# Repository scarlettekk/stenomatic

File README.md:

Stenomatic is an open source stenotype keyboard designed for an elegant yet inexpensive typing experience. This repository hosts all the files and information needed to produce one, which anyone can do for their own use. You may use your Stenomatic for any purpose you like, but you may not produce Stenomatics for the express purpose of selling them.

*Note: Photos of the keyboard in this document are of v2.0, when the Left S and * keys were rotated incorrectly, hence they only had 1u keycaps. This is fixed in the current version and 2u keycaps can be used.*

Stenomatic uses [Kailh Choc Pink switches](https://www.kailhswitch.com/mechanical-keyboard-switches/choc-pro-pink-keyboard-switch.html) for the most similar experience to a professional stenotype machine.

[Stenomatic](https://github.com/scarlettekk/stenomatic) © 2024 by [Cora Shuryn](https://github.com/scarlettekk/) is licensed under [CC BY-NC-SA 4.0](https://creativecommons.org/licenses/by-nc-sa/4.0/?ref=chooser-v1)

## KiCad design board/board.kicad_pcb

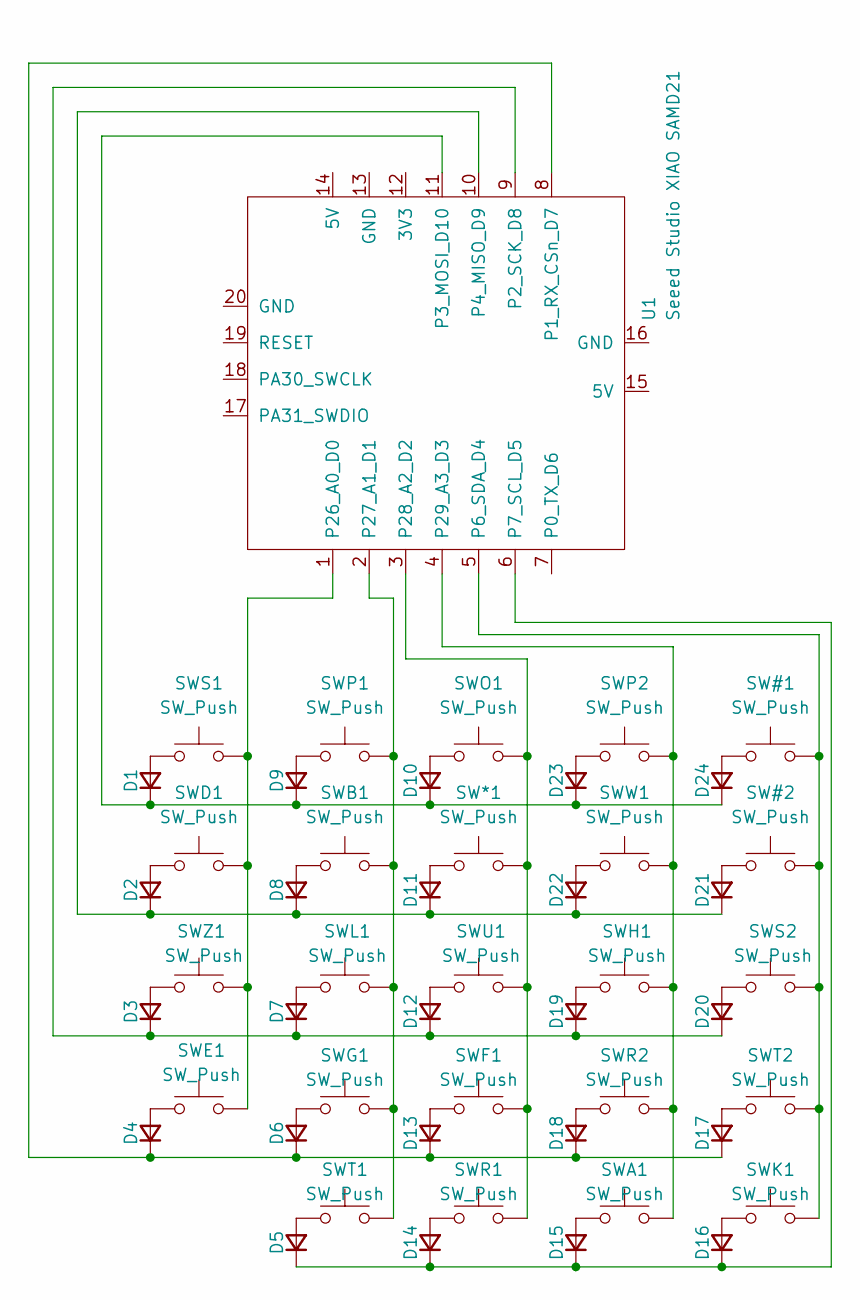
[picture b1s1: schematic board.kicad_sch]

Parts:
D1, D2, D3, D4, D5, D6, D7, D8, D9, D10, D11, D12, D13, D14, D15, D16, D17, D18, D19, D20, D21, D22, D23, D24: D_Small; D_DO-41_SOD81_P7.62mm_Horizontal
SW#1, SW#2: SW_Push; SW_Matias_1.00u
SW*1: SW_Push; SW_Matias_1.00u
SWA1: SW_Push; SW_Matias_1.00u
SWB1: SW_Push; SW_Matias_1.00u
SWD1: SW_Push; SW_Matias_1.00u
SWE1: SW_Push; SW_Matias_1.00u
SWF1: SW_Push; SW_Matias_1.00u
SWG1: SW_Push; SW_Matias_1.00u
SWH1: SW_Push; SW_Matias_1.00u
SWK1: SW_Push; SW_Matias_1.00u
SWL1: SW_Push; SW_Matias_1.00u
SWO1: SW_Push; SW_Matias_1.00u
SWP1, SWP2: SW_Push; SW_Matias_1.00u
SWR1, SWR2: SW_Push; SW_Matias_1.00u
SWS1, SWS2: SW_Push; SW_Matias_1.00u
SWT1, SWT2: SW_Push; SW_Matias_1.00u
SWU1: SW_Push; SW_Matias_1.00u
SWW1: SW_Push; SW_Matias_1.00u
SWZ1: SW_Push; SW_Matias_1.00u
U1: Seeed Studio XIAO SAMD21; XIAO-SAMD21-RP2040-14P-2.54-21X17.8MM (Seeeduino XIAO)

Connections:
unnamed: D1.2 (A), SWS1.1
unnamed: D1.1 (K), D9.1 (K), D10.1 (K), D23.1 (K), D24.1 (K), U1.11 (P3_MOSI_D10)
unnamed: D2.2 (A), SWD1.1
unnamed: D3.2 (A), SWZ1.1
unnamed: D4.2 (A), SWE1.1
unnamed: D5.2 (A), SWT1.1
unnamed: D6.2 (A), SWG1.1
unnamed: D7.2 (A), SWL1.1
unnamed: D8.2 (A), SWB1.1
unnamed: D9.2 (A), SWP1.1
unnamed: D10.2 (A), SWO1.1
unnamed: D11.2 (A), SW*1.1
unnamed: D2.1 (K), D8.1 (K), D11.1 (K), D21.1 (K), D22.1 (K), U1.10 (P4_MISO_D9)
unnamed: D12.2 (A), SWU1.1
unnamed: D3.1 (K), D7.1 (K), D12.1 (K), D19.1 (K), D20.1 (K), U1.9 (P2_SCK_D8)
unnamed: D13.2 (A), SWF1.1
unnamed: D4.1 (K), D6.1 (K), D13.1 (K), D17.1 (K), D18.1 (K), U1.8 (P1_RX_CSn_D7)
unnamed: D14.2 (A), SWR1.1
unnamed: D5.1 (K), D14.1 (K), D15.1 (K), D16.1 (K), U1.6 (P7_SCL_D5)
unnamed: D15.2 (A), SWA1.2
unnamed: D16.2 (A), SWK1.1
unnamed: D17.2 (A), SWT2.1
unnamed: D18.2 (A), SWR2.2
unnamed: D19.2 (A), SWH1.2
unnamed: D20.2 (A), SWS2.1
unnamed: D21.2 (A), SW#2.1
unnamed: D22.2 (A), SWW1.2
unnamed: D23.2 (A), SWP2.2
unnamed: D24.2 (A), SW#1.1
unnamed: SW#1.2, SW#2.2, SWK1.2, SWS2.2, SWT2.2, U1.5 (P6_SDA_D4)
unnamed: SWD1.2, SWE1.2, SWS1.2, SWZ1.2, U1.1 (P26_A0_D0)
unnamed: SWB1.2, SWG1.2, SWL1.2, SWP1.2, SWT1.2, U1.2 (P27_A1_D1)
unnamed: SW*1.2, SWF1.2, SWO1.2, SWR1.2, SWU1.2, U1.3 (P28_A2_D2)
unnamed: SWA1.1, SWH1.1, SWP2.1, SWR2.1, SWW1.1, U1.4 (P29_A3_D3)

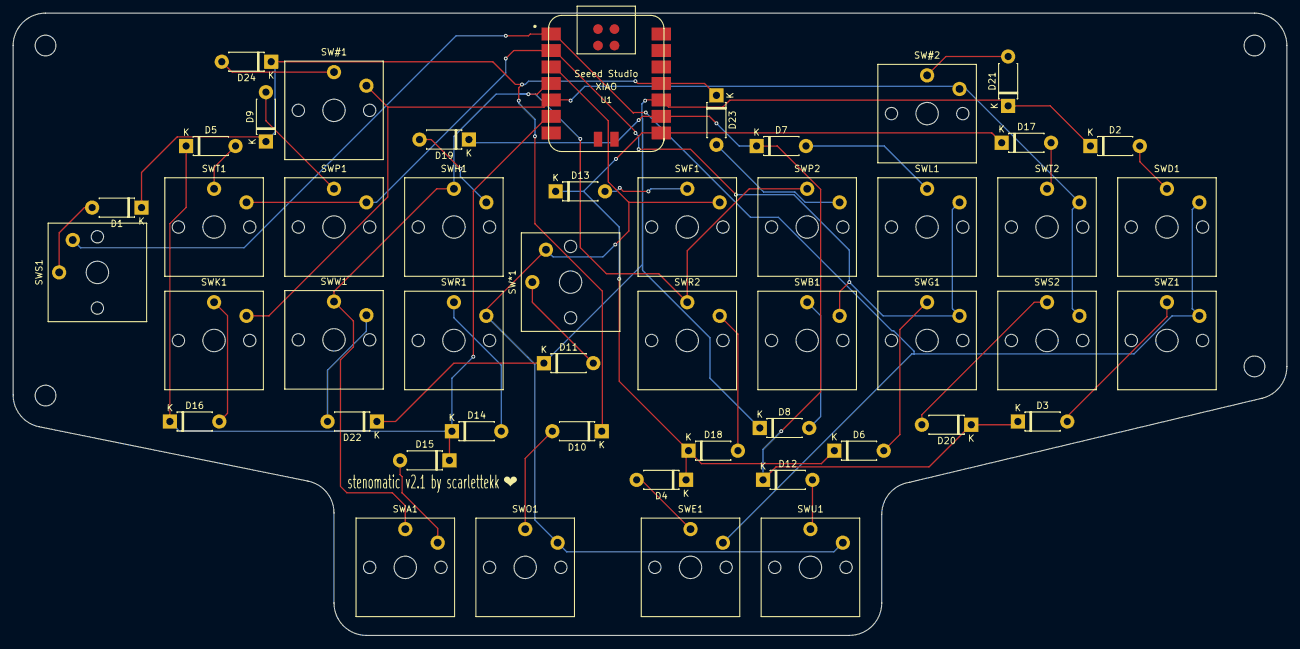
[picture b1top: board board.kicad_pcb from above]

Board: 2 copper layers, 196.5 x 96.0 mm, 49 parts (0 on the bottom side), 34 nets.

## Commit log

2024-10-09 Fix markdown
2024-10-09 switch to THT diodes for ease of installation
2024-10-09 fixed untracked files
2024-10-09 update jlcpcb schematics
2024-10-09 missing trace
2024-10-09 remove spurious silkscreen
2024-10-09 mounting holes
2024-10-13 add firmware, switch to choc keys, rewire (v2)
2024-10-13 add 3d models
2024-10-13 Postpone standalone version
2024-10-13 update jlcpcb files
2024-10-13 add another mounting hole
2024-12-30 update firmware to txbolt
2024-12-30 v2.1
